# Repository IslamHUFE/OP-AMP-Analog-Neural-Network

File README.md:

## This shit was extremely difficult

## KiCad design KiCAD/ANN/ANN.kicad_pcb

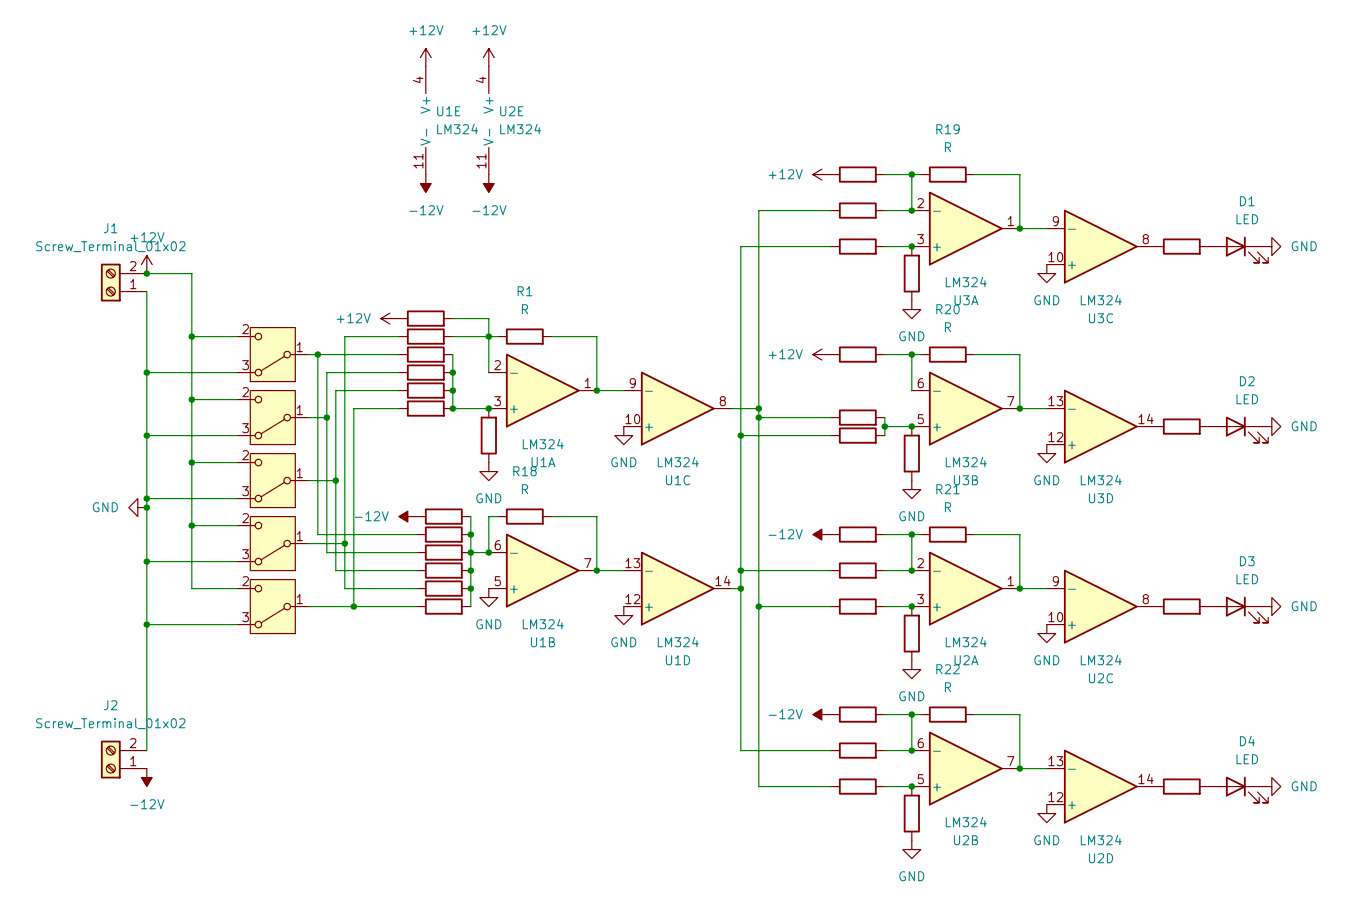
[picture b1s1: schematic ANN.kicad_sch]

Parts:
D1, D2, D3, D4: LED; LED_D3.0mm
J1, J2: Screw_Terminal_01x02; TerminalBlock_MetzConnect_Type011_RT05502HBLC_1x02_P5.00mm_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
R1, R2, R3, R4, R5, R6, R7, R8, R9, R10, R11, R12, R13, R14, R15, R16, R17, R18, R19, R20, R21, R22, R23, R24, R25, R26, R27, R28, R29, R30, R31, R32, R33, R34, R35, R36, R37, R38, R39: R; R_Axial_DIN0204_L3.6mm_D1.6mm_P5.08mm_Horizontal
SW1, SW2, SW3, SW4, SW5: SW_Wuerth_450301014042; SW_Slide-03_Wuerth-WS-SLTV_10x2.5x6.4_P2.54mm
U1, U2, U3: LM324; DIP-14_W7.62mm

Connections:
+12V: J1.2, R8.1, R25.1, R28.1, SW1.2 (C), SW2.2 (C), SW3.2 (C), SW4.2 (C), SW5.2 (C), U1.4 (V+), U2.4 (V+)
-12V: J2.1, R31.1, R32.1, R33.1, U1.11 (V-), U2.11 (V-)
GND: D1.1 (K), D2.1 (K), D3.1 (K), D4.1 (K), J1.1, J2.2, R6.1, R14.1, R15.1, R16.1, R17.1, SW1.3 (A), SW2.3 (A), SW3.3 (A), SW4.3 (A), SW5.3 (A), U1.5 (+), U1.10 (+), U1.12 (+), U2.10 (+), U2.12 (+), U3.10 (+), U3.12 (+)
unnamed: D1.2 (A), R36.2
unnamed: D2.2 (A), R37.2
unnamed: D3.2 (A), R38.2
unnamed: D4.2 (A), R39.2
unnamed: R23.1, R26.1, R30.1, R35.1, U1.8
unnamed: R24.1, R27.1, R29.1, R34.1, U1.14
unnamed: R36.1, U3.8
unnamed: R37.1, U3.14
unnamed: R38.1, U2.8
unnamed: R39.1, U2.14
unnamed: R5.1, R9.1, SW1.1 (B)
unnamed: R2.1, R10.1, SW2.1 (B)
unnamed: R3.1, R11.1, SW3.1 (B)
unnamed: R7.1, R12.1, SW4.1 (B)
unnamed: R4.1, R13.1, SW5.1 (B)
unnamed: R2.2, R3.2, R4.2, R5.2, R6.2, U1.3 (+)
unnamed: R1.1, R7.2, R8.2, U1.2 (-)
unnamed: R9.2, R10.2, R11.2, R12.2, R13.2, R18.1, R32.2, U1.6 (-)
unnamed: R1.2, U1.1, U1.9 (-)
unnamed: R18.2, U1.7, U1.13 (-)
unnamed: R16.2, R30.2, U2.3 (+)
unnamed: R21.1, R29.2, R31.2, U2.2 (-)
unnamed: R17.2, R35.2, U2.5 (+)
unnamed: R22.1, R33.2, R34.2, U2.6 (-)
unnamed: R21.2, U2.1, U2.9 (-)
unnamed: R22.2, U2.7, U2.13 (-)
unnamed: R14.2, R24.2, U3.3 (+)
unnamed: R19.1, R23.2, R25.2, U3.2 (-)
unnamed: R15.2, R26.2, R27.2, U3.5 (+)
unnamed: R20.1, R28.2, U3.6 (-)
unnamed: R19.2, U3.1, U3.9 (-)
unnamed: R20.2, U3.7, U3.13 (-)

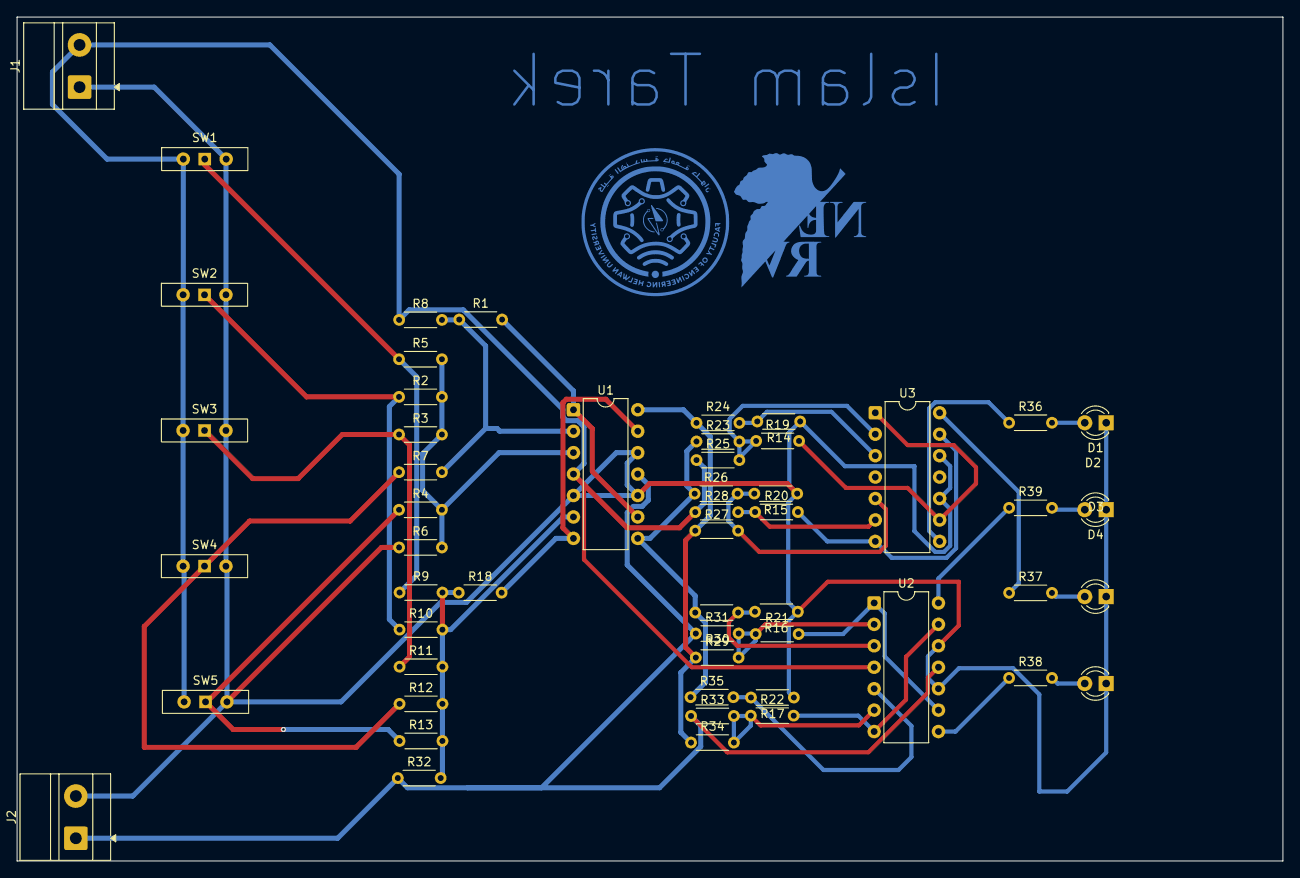
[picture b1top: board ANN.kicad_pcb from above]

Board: 2 copper layers, 150.0 x 100.0 mm, 53 parts (0 on the bottom side), 35 nets.

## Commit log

2026-04-27 intial commit
2026-04-29 Restore original content in untitled.m
2026-05-01 organising
2026-05-08 refresh
2026-05-08 LICENSE
2026-05-10 Adding عبدو work
